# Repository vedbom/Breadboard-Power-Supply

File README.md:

# Breadboard Power Supply
This is a custom PCB for a breadboard power supply I created to use parts already available in my parts bin. It utilizes LM317 and LM7805 voltage regulators to provide an output voltage of 5V or a variable output voltage range depending on the supply voltage. Power is supplied to the circuit via an external power supply using a barrel jack connector. There are two large switches that turn the circuit on/off and switch the output voltage between 5V or the variable voltage. An LED indicates whether the circuit is turned on/off to prevent short circuits during experimentation on the breadboard. The PCB can be connected directly to the power rails on a standard breadboard using the pin headers.

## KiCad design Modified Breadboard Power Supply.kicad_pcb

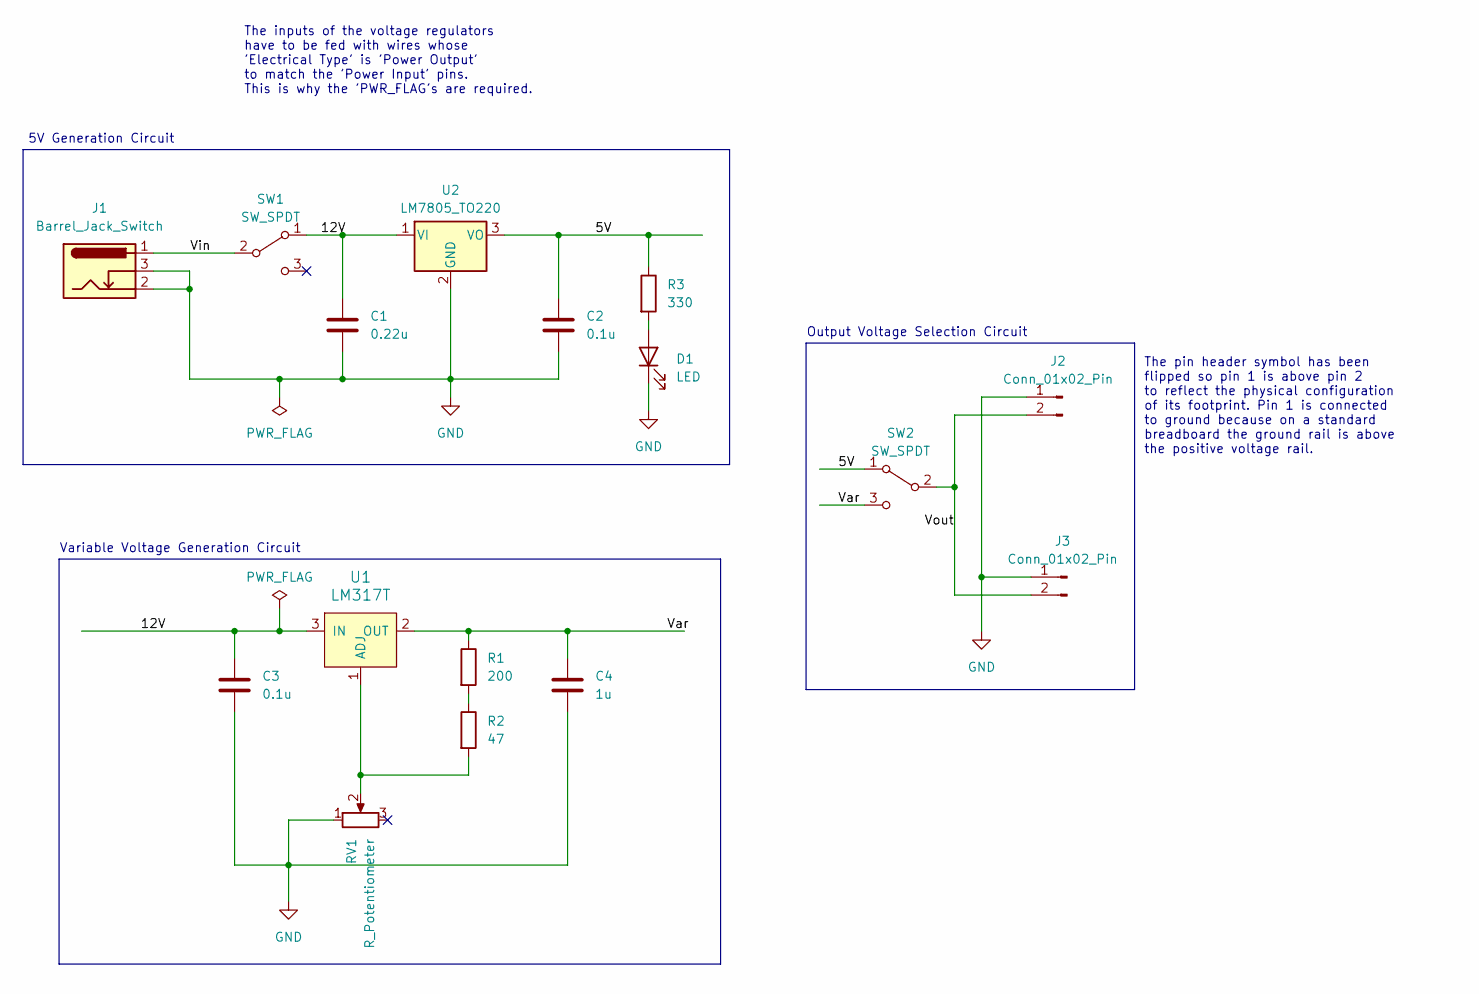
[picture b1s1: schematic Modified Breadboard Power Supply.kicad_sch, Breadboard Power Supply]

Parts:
C1: 0.22u; C_Disc_D5.0mm_W2.5mm_P2.50mm
C2, C3: 0.1u; C_Disc_D5.0mm_W2.5mm_P2.50mm
C4: 1u; C_Disc_D5.0mm_W2.5mm_P2.50mm
D1: LED; LED_D3.0mm
J1: Barrel_Jack_Switch; BarrelJack_GCT_DCJ200-10-A_Horizontal
J2, J3: Conn_01x02_Pin; PinHeader_1x02_P2.54mm_Vertical
R1: 200; R_Axial_DIN0204_L3.6mm_D1.6mm_P7.62mm_Horizontal
R2: 47; R_Axial_DIN0204_L3.6mm_D1.6mm_P7.62mm_Horizontal
R3: 330; R_Axial_DIN0204_L3.6mm_D1.6mm_P7.62mm_Horizontal
RV1: R_Potentiometer; blue-trimmer-potentiometer
SW1, SW2: SW_SPDT; large-red-toggle-switch-SPDT
U1: LM317T; TO-220-3; MPN LM317T; Digi-Key_PN 497-1575-5-ND
U2: LM7805_TO220; TO-220-3_Vertical

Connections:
/5V: C2.1, R3.1, SW2.1 (A), U2.3 (VO)
/12V: C1.1, C3.1, SW1.1 (A), U1.3 (IN), U2.1 (VI)
/Var: C4.1, R1.1, SW2.3 (C), U1.2 (OUT)
/Vin: J1.1, SW1.2 (B)
/Vout: J2.2, J3.2, SW2.2 (B)
GND: C1.2, C2.2, C3.2, C4.2, D1.1 (K), J1.2, J1.3, J2.1, J3.1, RV1.1, U2.2 (GND)
unnamed: D1.2 (A), R3.2
unnamed: R1.2, R2.1
unnamed: R2.2, RV1.2, U1.1 (ADJ)

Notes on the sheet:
The pin header symbol has been flipped so pin 1 is above pin 2 to reflect the physical configuration of its footprint. Pin 1 is connected to ground because on a standard breadboard the ground rail is above the positive voltage rail.
Variable Voltage Generation Circuit
The inputs of the voltage regulators have to be fed with wires whose 'Electrical Type' is 'Power Output' to match the 'Power Input' pins. This is why the 'PWR_FLAG's are required.
Output Voltage Selection Circuit
5V Generation Circuit

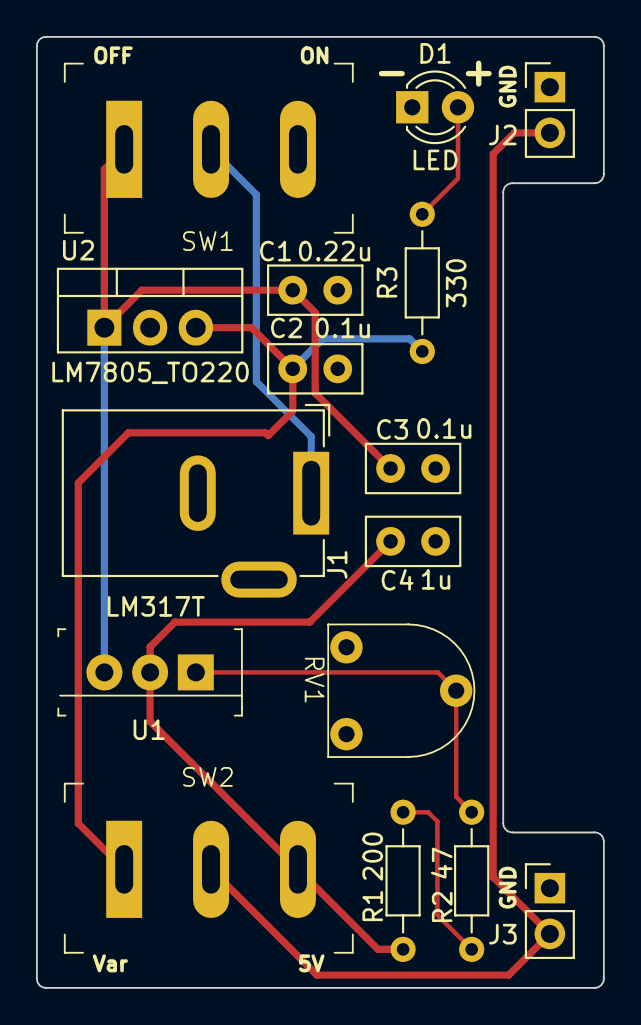
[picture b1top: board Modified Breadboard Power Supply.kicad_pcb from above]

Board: 2 copper layers, 31.5 x 52.8 mm, 16 parts (0 on the bottom side), 9 nets.

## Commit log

2025-01-27 Added images of the PCB
